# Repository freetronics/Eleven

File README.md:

Freetronics Eleven R3
=============================
Copyright 2010-2012 Freetronics Pty Ltd  
Freetronics site:  www.freetronics.com  
Freetronics email: info@freetronics.com  

The Eleven is a 100% Arduino Compatible Board, based on the Arduino
Uno reference design, but with improvements and updates for ease of
use, cost and getting started.

Features:

 * Prototyping area
 * LEDs visible on the edge
 * Mini-USB Connector
 * Overlay guide where you need it (both top and bottom)
 * D13 pin works for everything
 * Mounting holes and power pads
 * All connections in the same place

You can view more at our product page at:

  http://www.freetronics.com/eleven

INSTALLATION
------------
The design is saved as an EAGLE project. EAGLE PCB design software is
available from www.cadsoftusa.com free for non-commercial use. To use
this project download it and place the directory containing these files
into the "eagle" directory on your computer. Then open EAGLE and
navigate to Projects -> eagle -> Eleven.

DISTRIBUTION
------------
The specific terms of distribution of this project are governed by the
license referenced below.

LICENSE
-------
This work is licensed under the
Creative Commons Attribution-Share Alike License.  
To view a copy of this license, visit

  http://creativecommons.org/licenses/by-sa/3.0/  
  http://creativecommons.org/licenses/by-sa/3.0/legalcode

or send a letter to

  Creative Commons  
  171 Second Street, Suite 300  
  San Francisco  
  California, 94105  
  USA

The "license" folder within this repository also contains copies of the
licences referenced above.

CREDITS
-------
The Eleven was designed by Marc Alexander (marc@freetronics.com) and
Jonathan Oxer (jon@freetronics.com) inspired by work by the Arduino
team (www.arduino.cc/playground/Main/People) which includes:

 * Massimo Banzi
 * David Cuartielles
 * Tom Igoe
 * Gianluca Martino
 * David A. Mellis

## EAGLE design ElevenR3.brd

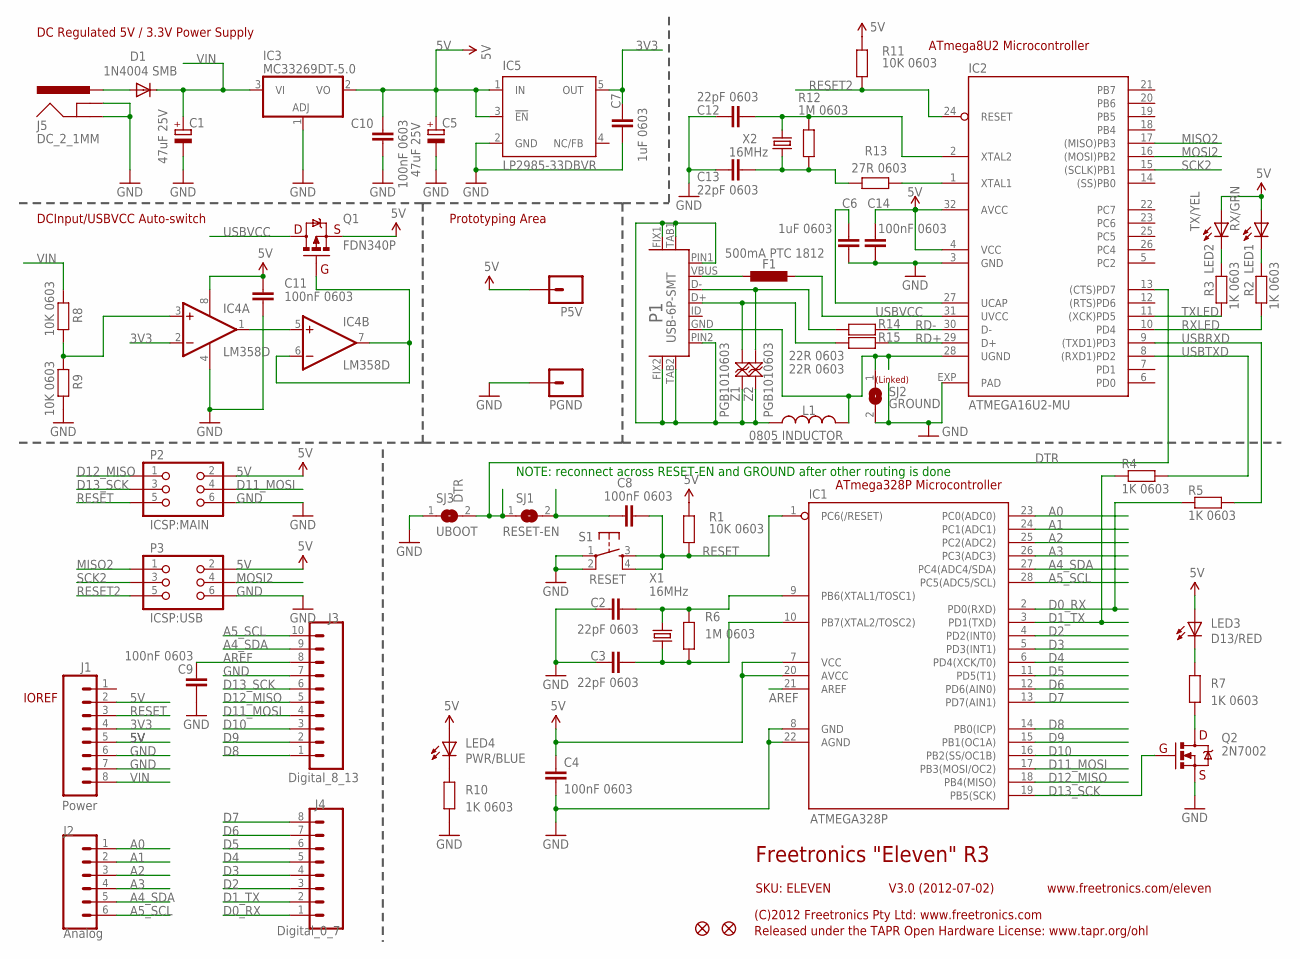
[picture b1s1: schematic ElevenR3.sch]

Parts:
C1, C5: 47uF 25V; PANASONIC_D
C2, C3, C12, C13: 22pF 0603; C0603
C4, C8, C9, C10, C11, C14: 100nF 0603; C0603
C6, C7: 1uF 0603; C0603
D1: 1N4004 SMB; SMA-DIODE
F1: 500mA PTC 1812; L1812
IC1: ATMEGA328P; DIL28-3
IC2: ATMEGA16U2-MU; ATMEL_QFN32
IC3: MC33269DT-5.0; DPACK
IC4: LM358D; SO08
IC5: LP2985-33DBVR; TEXAS_SOT23-DBV
J1: Power; 1X08-S
J2: Analog; 1X06-S
J3: Digital_8_13; 1X10-S
J4: Digital_0_7; 1X08-S
J5: DC_2_1MM; POWER_JACK_SLOTS
L1: 0805 INDUCTOR; 0805-LARGE
LED1: RX/GRN; LED-0603
LED2: TX/YEL; LED-0603
LED3: D13/RED; LED-0603
LED4: PWR/BLUE; LED-0603
P1: USB-6P-SMT; USB-MICROB-MB05PMXX
P2: ICSP:MAIN; 2X03PTH
P3: ICSP:USB; 2X03PTH
P5V: M01SMD; LUXEON-PAD
PGND: M01SMD; LUXEON-PAD
Q1: FDN340P; SOT23-3
Q2: 2N7002; SOT23-3
R1, R8, R9, R11: 10K 0603; R0603
R2, R3, R4, R5, R7, R10: 1K 0603; R0603
R6, R12: 1M 0603; R0603
R13: 27R 0603; R0603
R14, R15: 22R 0603; R0603
S1: RESET; TACTILE_SMD-6MM
SJ1: RESET-EN; SJ
SJ2: GROUND; SJ
SJ3: UBOOT; SJ
U$5, U$14: FIDUCIAL1X2.5; FIDUCIAL-1X2.5
X1, X2: 16MHz; HC49U-V
Z1, Z2: PGB1010603; TVS0603

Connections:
3V3: C7.2, IC4.2 (-IN), IC5.5 (OUT), J1.4
5V: C4.1, C5.+, C10.1, C11.1, C14.1, IC1.7 (VCC), IC1.20 (AVCC), IC2.4 (VCC), IC2.32 (AVCC), IC3.2 (VO), IC4.8 (V+), IC5.1 (IN), IC5.3 (!EN), J1.2, J1.5, LED1.A, LED2.A, LED3.A, LED4.A, P2.2, P3.2, P5V.P$1, Q1.2 (S), R1.2, R11.2
A0: IC1.23 (PC0(ADC0)), J2.1
A1: IC1.24 (PC1(ADC1)), J2.2
A2: IC1.25 (PC2(ADC2)), J2.3
A3: IC1.26 (PC3(ADC3)), J2.4
A4_SDA: IC1.27 (PC4(ADC4/SDA)), J2.5, J3.9
A5_SCL: IC1.28 (PC5(ADC5/SCL)), J2.6, J3.10
AREF: C9.1, IC1.21 (AREF), J3.8
D0_RX: IC1.2 (PD0(RXD)), J4.1, R5.1
D1_TX: IC1.3 (PD1(TXD)), J4.2, R4.1
D2: IC1.4 (PD2(INT0)), J4.3
D3: IC1.5 (PD3(INT1)), J4.4
D4: IC1.6 (PD4(XCK/T0)), J4.5
D5: IC1.11 (PD5(T1)), J4.6
D6: IC1.12 (PD6(AIN0)), J4.7
D7: IC1.13 (PD7(AIN1)), J4.8
D8: IC1.14 (PB0(ICP)), J3.1
D9: IC1.15 (PB1(OC1A)), J3.2
D10: IC1.16 (PB2(SS/OC1B)), J3.3
D11_MOSI: IC1.17 (PB3(MOSI/OC2)), J3.4, P2.4
D12_MISO: IC1.18 (PB4(MISO)), J3.5, P2.1
D13_SCK: IC1.19 (PB5(SCK)), J3.6, P2.3, Q2.1 (G)
DTR: IC2.13 ((CTS)PD7), SJ1.1, SJ3.2
GND: C1.-, C2.1, C3.1, C4.2, C5.-, C6.2, C7.1, C9.2, C10.2, C11.2, C12.1, C13.1, C14.2, IC1.8 (GND), IC1.22 (AGND), IC2.3 (GND), IC2.EXP (PAD), IC3.1 (ADJ), IC4.4 (V-), IC5.2 (GND), J1.6, J1.7, J3.7, J5.GND, J5.GNDBREAK, P2.6, P3.6, PGND.P$1, Q2.2 (S), R9.1, R10.1, S1.1, S1.2, SJ2.2, SJ3.1
MISO2: IC2.17 ((MISO)PB3), P3.1
MOSI2: IC2.16 ((MOSI)PB2), P3.4
unnamed: C8.1, SJ1.2
unnamed: IC2.1 (XTAL1), R13.1
unnamed: L1.1, P1.FIX1, P1.FIX2, P1.PIN1, P1.PIN2, P1.TAB1, P1.TAB2, Z1.2, Z2.2
unnamed: LED3.C, R7.2
unnamed: C2.2, IC1.9 (PB6(XTAL1/TOSC1)), R6.2, X1.2
unnamed: Q2.3 (D), R7.1
unnamed: C3.2, IC1.10 (PB7(XTAL2/TOSC2)), R6.1, X1.1
unnamed: D1.A, J5.PWR
unnamed: IC4.3 (+IN), R8.1, R9.2
unnamed: IC4.1 (OUT), IC4.5 (+IN)
unnamed: LED1.C, R2.2
unnamed: IC4.6 (-IN), IC4.7 (OUT), Q1.1 (G)
unnamed: LED2.C, R3.2
unnamed: LED4.C, R10.2
unnamed: P1.D+, R15.2, Z1.1
unnamed: P1.D-, R14.2, Z2.1
unnamed: C12.2, IC2.2 (XTAL2), R12.2, X2.2
unnamed: C13.2, R12.1, R13.2, X2.1
unnamed: F1.1, P1.VBUS
unnamed: C6.1, IC2.27 (UCAP)
RD+: IC2.29 (D+), R15.1
RD-: IC2.30 (D-), R14.1
RESET: C8.2, IC1.1 (PC6(/RESET)), J1.3, P2.5, R1.1, S1.3, S1.4
RESET2: IC2.24 (RESET), P3.5, R11.1
RXLED: IC2.10 (PD4), R2.1
SCK2: IC2.15 ((SCLK)PB1), P3.3
TXLED: IC2.11 ((XCK)PD5), R3.1
UGND: IC2.28 (UGND), L1.2, P1.GND, SJ2.1
USBRXD: IC2.9 ((TXD1)PD3), R5.2
USBTXD: IC2.8 ((RXD1)PD2), R4.2
USBVCC: F1.2, IC2.31 (UVCC), Q1.3 (D)
VIN: C1.+, D1.C, IC3.3 (VI), J1.8, R8.2

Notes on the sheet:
Prototyping Area
DCInput/USBVCC Auto-switch
DC Regulated 5V / 3.3V Power Supply
ATmega328P Microcontroller
ATmega8U2 Microcontroller
NOTE: reconnect across RESET-EN and GROUND after other routing is done
Freetronics "Eleven" R3
V3.0 (2012-07-02)
SKU: ELEVEN
(C)2012 Freetronics Pty Ltd: www.freetronics.com
Released under the TAPR Open Hardware License: www.tapr.org/ohl
www.freetronics.com/eleven
(Linked)
IOREF

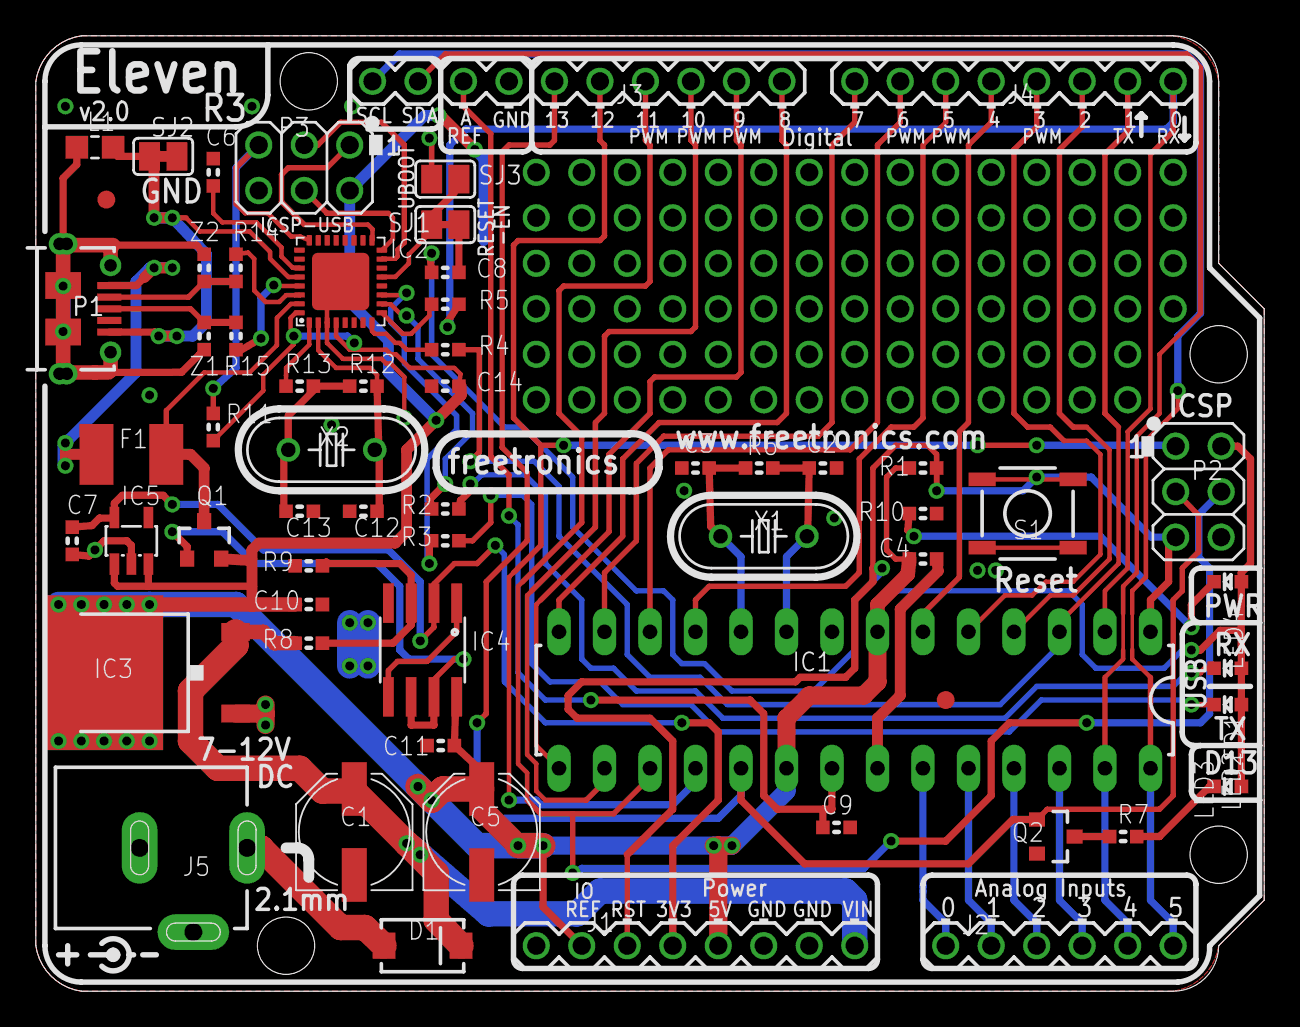
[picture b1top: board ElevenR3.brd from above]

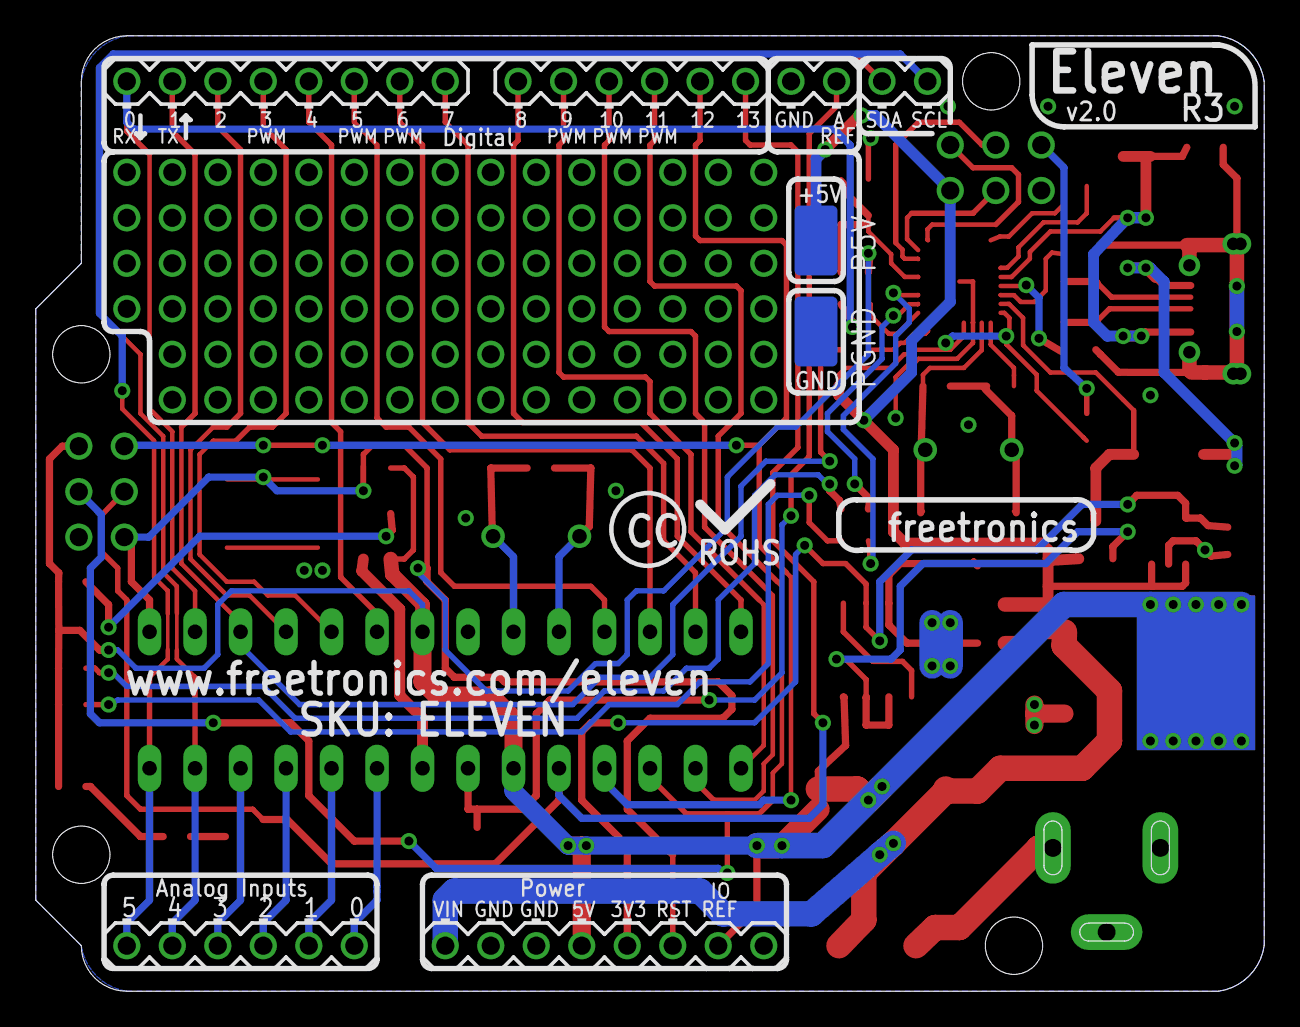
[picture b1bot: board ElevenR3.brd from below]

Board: 2 copper layers, 68.6 x 53.3 mm, 63 parts (2 on the bottom side), 59 nets.

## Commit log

2010-11-20 Imported project
2010-11-21 Isolated USB GND from signal GND; fixed value of USB D series resistors
2010-11-21 Started moving 8U2 and associated parts into position
2010-11-21 Minor parts shuffling
2010-11-21 Removed link across RESET-EN to help airwires go to the right place until routing is done
2010-11-21 Removed C11; changed LED resistor values; separated headers on schematic
2011-01-03 Pre-release - last lookover
2011-01-03 Tweaks - designator layer
2011-01-05 Final - pre-inspection
2011-01-05 SKU on sch page, pdf recreated
2012-06-24 Beginning of conversion to R3
2012-06-24 Renamed project files
2012-06-24 Version updates
2012-06-26 Routed I2C and converted to microUSB
2012-07-03 Overlay, layout, and schematic tweaks
2012-07-03 Routing, position, and overlay tweaks
2012-07-04 Clearances
2012-07-05 Replaced uUSB footprint
2012-07-06 R3 updates
2012-07-06 Production release v2.0 after small revisions
2013-10-11 Improved formatting
2019-07-01 Replaced most parts using SuperHouse library to add 3D models
